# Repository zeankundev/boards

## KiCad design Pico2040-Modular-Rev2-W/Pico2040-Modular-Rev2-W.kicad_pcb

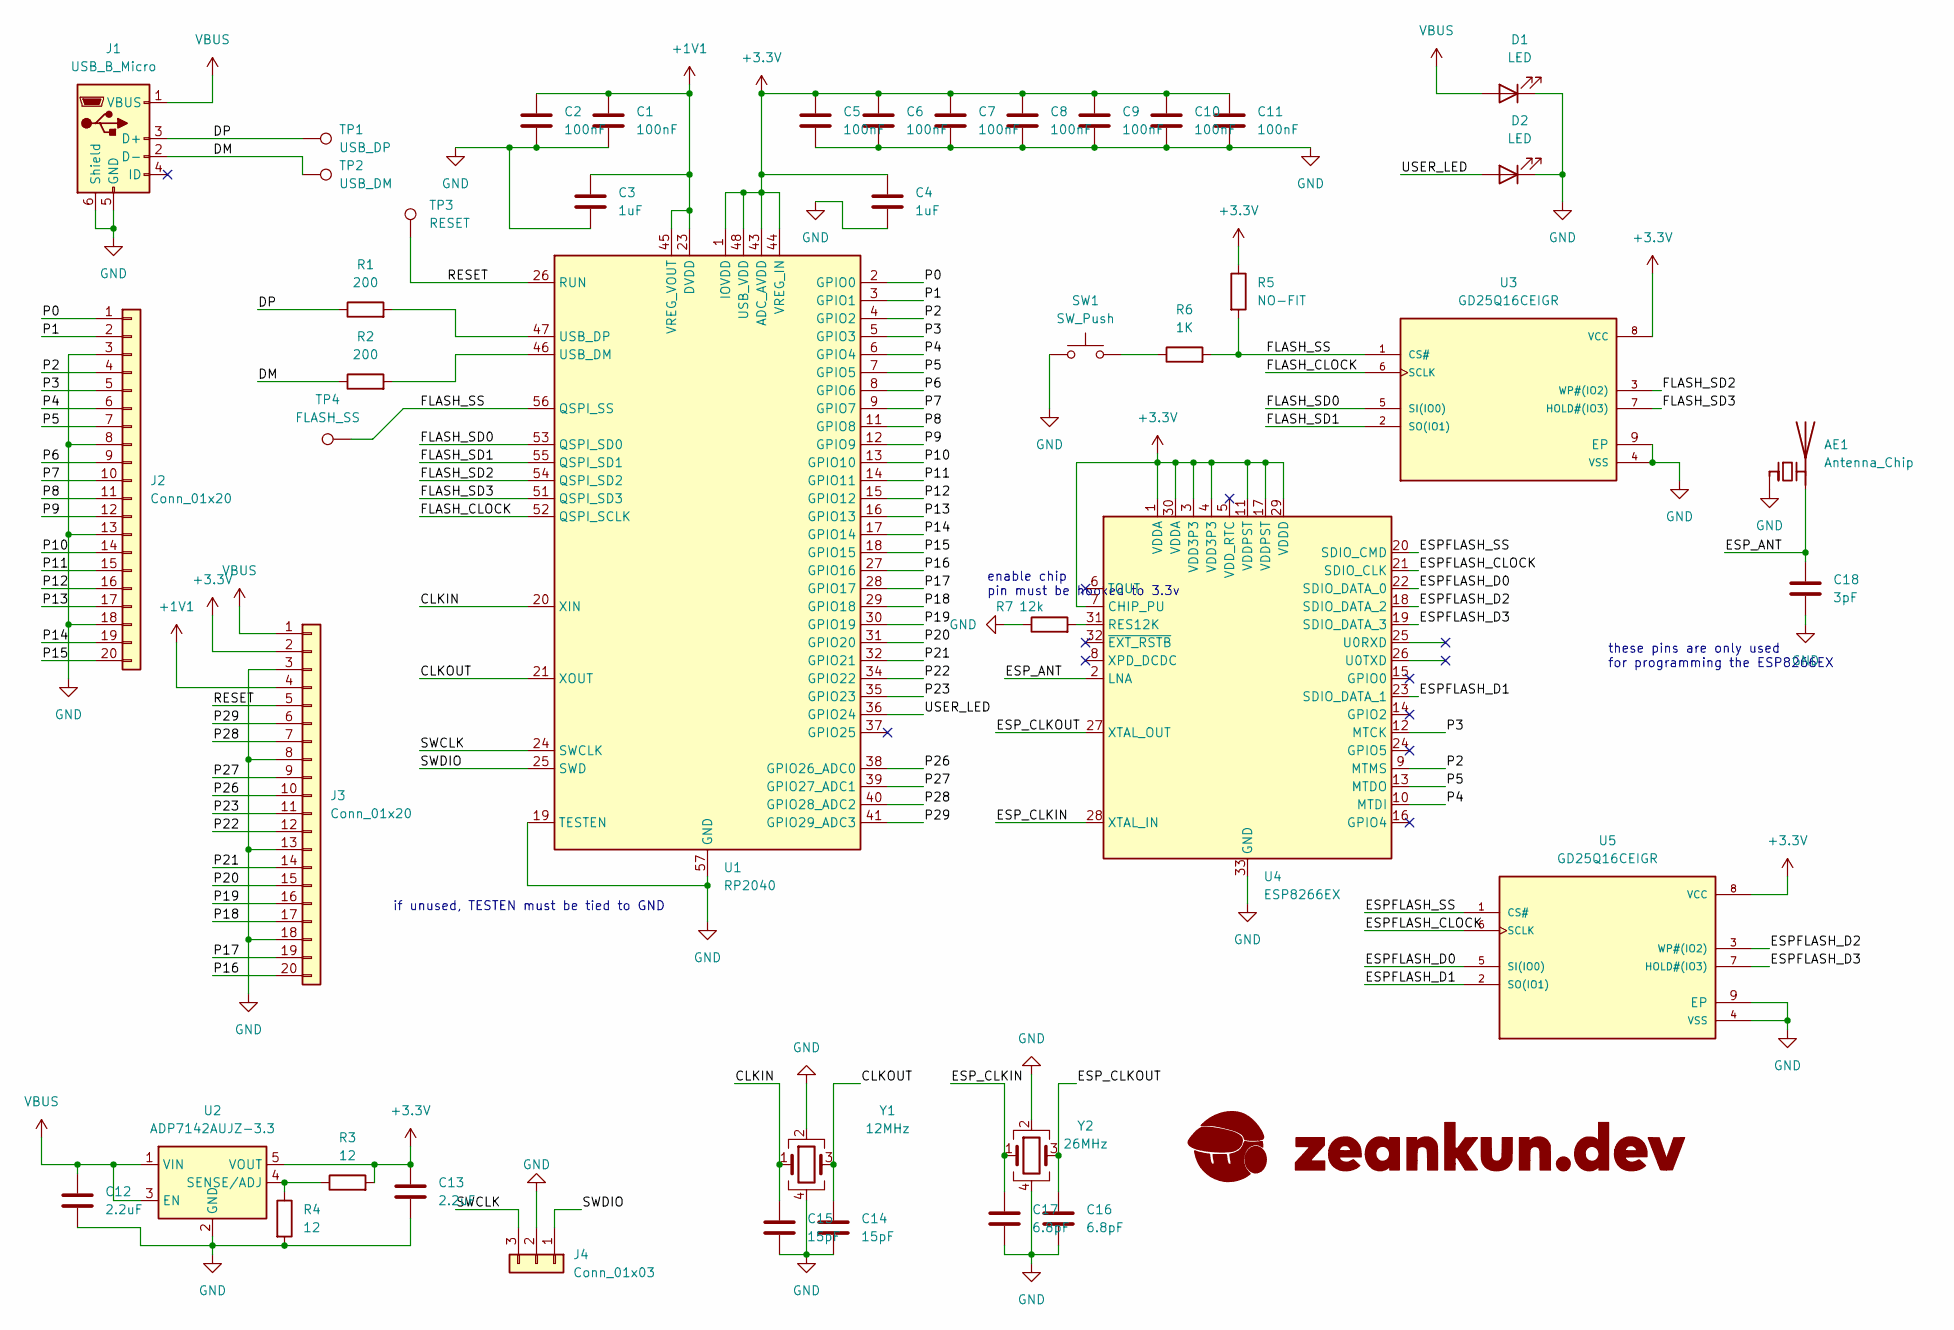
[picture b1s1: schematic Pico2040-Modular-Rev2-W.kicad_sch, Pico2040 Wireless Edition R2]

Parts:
AE1: Antenna_Chip; BroadWave_029mm
C1, C2, C5, C6, C7, C8, C9, C10, C11: 100nF; C_0201_0603Metric
C3, C4: 1uF; C_0201_0603Metric
C12, C13: 2.2uF; C_0201_0603Metric
C14, C15: 15pF; C_0201_0603Metric
C16, C17: 6.8pF; C_0201_0603Metric
C18: 3pF; C_0201_0603Metric
D1, D2: LED; LED_0201_0603Metric
J1: USB_B_Micro; USB_Micro-B_Amphenol_10103594-0001LF_Horizontal
J2, J3: Conn_01x20; PinHeader_1x20_2H_P2.54mm_Vertical
J4: Conn_01x03; PinHeader_1x03_P2.54mm_Vertical
R1, R2: 200; R_0201_0603Metric
R3, R4: 12; R_0201_0603Metric
R5: NO-FIT; R_0201_0603Metric
R6: 1K; R_0201_0603Metric
R7: 12k; R_0201_0603Metric
SW1: SW_Push; SW_Push_1P1T_NO_Vertical_Wuerth_434133025816
TP1: USB_DP; TestPoint_Pad_D1.0mm
TP2: USB_DM; TestPoint_Pad_D1.0mm
TP3: RESET; TestPoint_Pad_D1.0mm
TP4: FLASH_SS; TestPoint_Pad_D1.0mm
U1: RP2040; QFN-56-1EP_7x7mm_P0.4mm_EP3.2x3.2mm
U2: ADP7142AUJZ-3.3; TSOT-23-5
U3, U5: GD25Q16CEIGR; PSON50P200X300X50-9N; PARTREV 3.0
U4: ESP8266EX; QFN-32-1EP_5x5mm_P0.5mm_EP3.45x3.45mm
Y1: 12MHz; Crystal_SMD_2520-4Pin_2.5x2.0mm
Y2: 26MHz; Crystal_SMD_2016-4Pin_2.0x1.6mm

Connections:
+1V1: C1.1, C2.1, C3.1, J3.4, U1.23 (DVDD), U1.45 (VREG_VOUT), U1.50 (DVDD)
+3.3V: C4.1, C5.1, C6.1, C7.1, C8.1, C9.1, C10.1, C11.1, C13.1, J3.2, R3.2, R5.1, U1.1 (IOVDD), U1.10 (IOVDD), U1.22 (IOVDD), U1.33 (IOVDD), U1.42 (IOVDD), U1.43 (ADC_AVDD), U1.44 (VREG_IN), U1.48 (USB_VDD), U1.49 (IOVDD), U2.5 (VOUT), U3.8 (VCC), U4.1 (VDDA), U4.3 (VDD3P3), U4.4 (VDD3P3), U4.7 (CHIP_PU), U4.11 (VDDPST), U4.17 (VDDPST), U4.29 (VDDD), U4.30 (VDDA), U5.8 (VCC)
/CLKIN: C15.1, U1.20 (XIN), Y1.1
/CLKOUT: C14.1, U1.21 (XOUT), Y1.3
/DM: J1.2 (D-), R2.1, TP2.1
/DP: J1.3 (D+), R1.1, TP1.1
/ESPFLASH_CLOCK: U4.21 (SDIO_CLK), U5.6 (SCLK)
/ESPFLASH_D0: U4.22 (SDIO_DATA_0), U5.5 (SI(IO0))
/ESPFLASH_D1: U4.23 (SDIO_DATA_1), U5.2 (SO(IO1))
/ESPFLASH_D2: U4.18 (SDIO_DATA_2), U5.3 (WP#(IO2))
/ESPFLASH_D3: U4.19 (SDIO_DATA_3), U5.7 (HOLD#(IO3))
/ESPFLASH_SS: U4.20 (SDIO_CMD), U5.1 (CS#)
/ESP_ANT: AE1.2 (PCB_Trace), C18.1, U4.2 (LNA)
/ESP_CLKIN: C17.1, U4.28 (XTAL_IN), Y2.1
/ESP_CLKOUT: C16.1, U4.27 (XTAL_OUT), Y2.3
/FLASH_CLOCK: U1.52 (QSPI_SCLK), U3.6 (SCLK)
/FLASH_SD0: U1.53 (QSPI_SD0), U3.5 (SI(IO0))
/FLASH_SD1: U1.55 (QSPI_SD1), U3.2 (SO(IO1))
/FLASH_SD2: U1.54 (QSPI_SD2), U3.3 (WP#(IO2))
/FLASH_SD3: U1.51 (QSPI_SD3), U3.7 (HOLD#(IO3))
/FLASH_SS: R5.2, R6.2, TP4.1, U1.56 (QSPI_SS), U3.1 (CS#)
/P0: J2.1, U1.2 (GPIO0)
/P1: J2.2, U1.3 (GPIO1)
/P2: J2.4, U1.4 (GPIO2), U4.9 (MTMS)
/P3: J2.5, U1.5 (GPIO3), U4.12 (MTCK)
/P4: J2.6, U1.6 (GPIO4), U4.10 (MTDI)
/P5: J2.7, U1.7 (GPIO5), U4.13 (MTDO)
/P6: J2.9, U1.8 (GPIO6)
/P7: J2.10, U1.9 (GPIO7)
/P8: J2.11, U1.11 (GPIO8)
/P9: J2.12, U1.12 (GPIO9)
/P10: J2.14, U1.13 (GPIO10)
/P11: J2.15, U1.14 (GPIO11)
/P12: J2.16, U1.15 (GPIO12)
/P13: J2.17, U1.16 (GPIO13)
/P14: J2.19, U1.17 (GPIO14)
/P15: J2.20, U1.18 (GPIO15)
/P16: J3.20, U1.27 (GPIO16)
/P17: J3.19, U1.28 (GPIO17)
/P18: J3.17, U1.29 (GPIO18)
/P19: J3.16, U1.30 (GPIO19)
/P20: J3.15, U1.31 (GPIO20)
/P21: J3.14, U1.32 (GPIO21)
/P22: J3.12, U1.34 (GPIO22)
/P23: J3.11, U1.35 (GPIO23)
/P26: J3.10, U1.38 (GPIO26_ADC0)
/P27: J3.9, U1.39 (GPIO27_ADC1)
/P28: J3.7, U1.40 (GPIO28_ADC2)
/P29: J3.6, U1.41 (GPIO29_ADC3)
/RESET: J3.5, TP3.1, U1.26 (RUN)
/SWCLK: J4.3, U1.24 (SWCLK)
/SWDIO: J4.1, U1.25 (SWD)
/USER_LED: D2.2 (A), U1.36 (GPIO24)
GND: AE1.1 (FEED), C1.2, C2.2, C3.2, C4.2, C5.2, C6.2, C7.2, C8.2, C9.2, C10.2, C11.2, C12.2, C13.2, C14.2, C15.2, C16.2, C17.2, C18.2, D1.1 (K), D2.1 (K), J1.5 (GND), J1.6 (Shield), J2.3, J2.8, J2.13, J2.18, J3.3, J3.8, J3.13, J3.18, J4.2, R4.2, R7.1, SW1.1, U1.19 (TESTEN), U1.57 (GND), U2.2 (GND), U3.4 (VSS), U3.9 (EP), U4.33 (GND), U5.4 (VSS), U5.9 (EP), Y1.2, Y1.4, Y2.2, Y2.4
unnamed: R6.1, SW1.2
unnamed: R2.2, U1.46 (USB_DM)
unnamed: R1.2, U1.47 (USB_DP)
unnamed: R3.1, R4.1, U2.4 (SENSE/ADJ)
unnamed: R7.2, U4.31 (RES12K)
VBUS: C12.1, D1.2 (A), J1.1 (VBUS), J3.1, U2.1 (VIN), U2.3 (EN)

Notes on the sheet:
these pins are only used for programming the ESP8266EX
enable chip pin must be hooked to 3.3v
if unused, TESTEN must be tied to GND

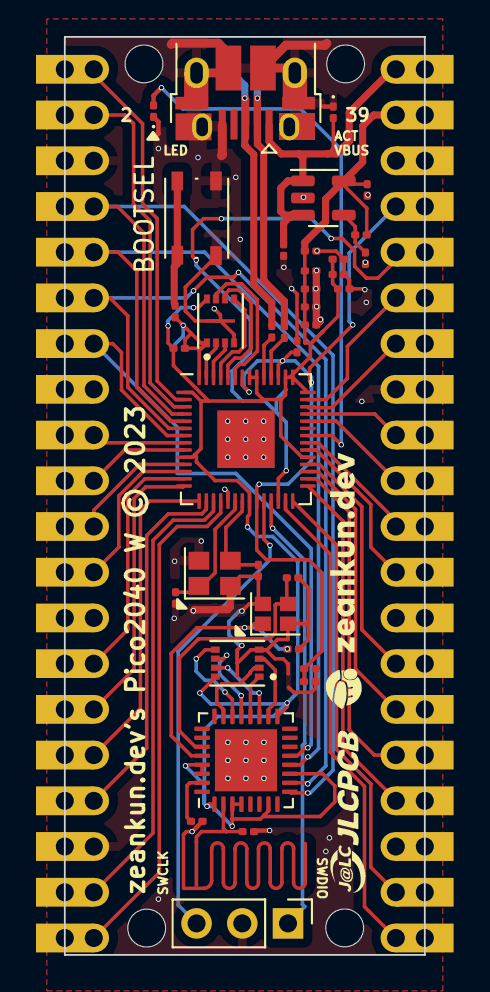
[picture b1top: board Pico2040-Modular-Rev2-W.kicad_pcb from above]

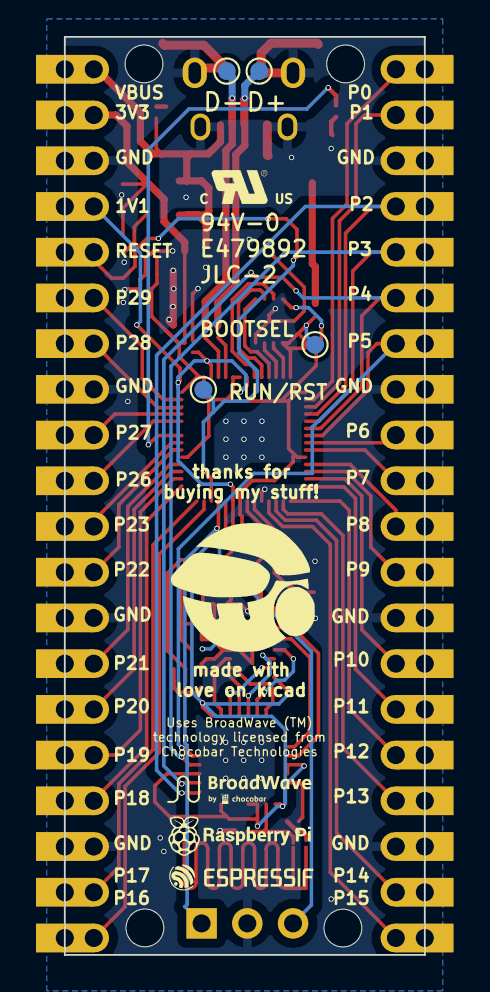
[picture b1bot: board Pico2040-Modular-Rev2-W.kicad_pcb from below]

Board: 2 copper layers, 20.0 x 51.0 mm, 44 parts (5 on the bottom side), 60 nets.

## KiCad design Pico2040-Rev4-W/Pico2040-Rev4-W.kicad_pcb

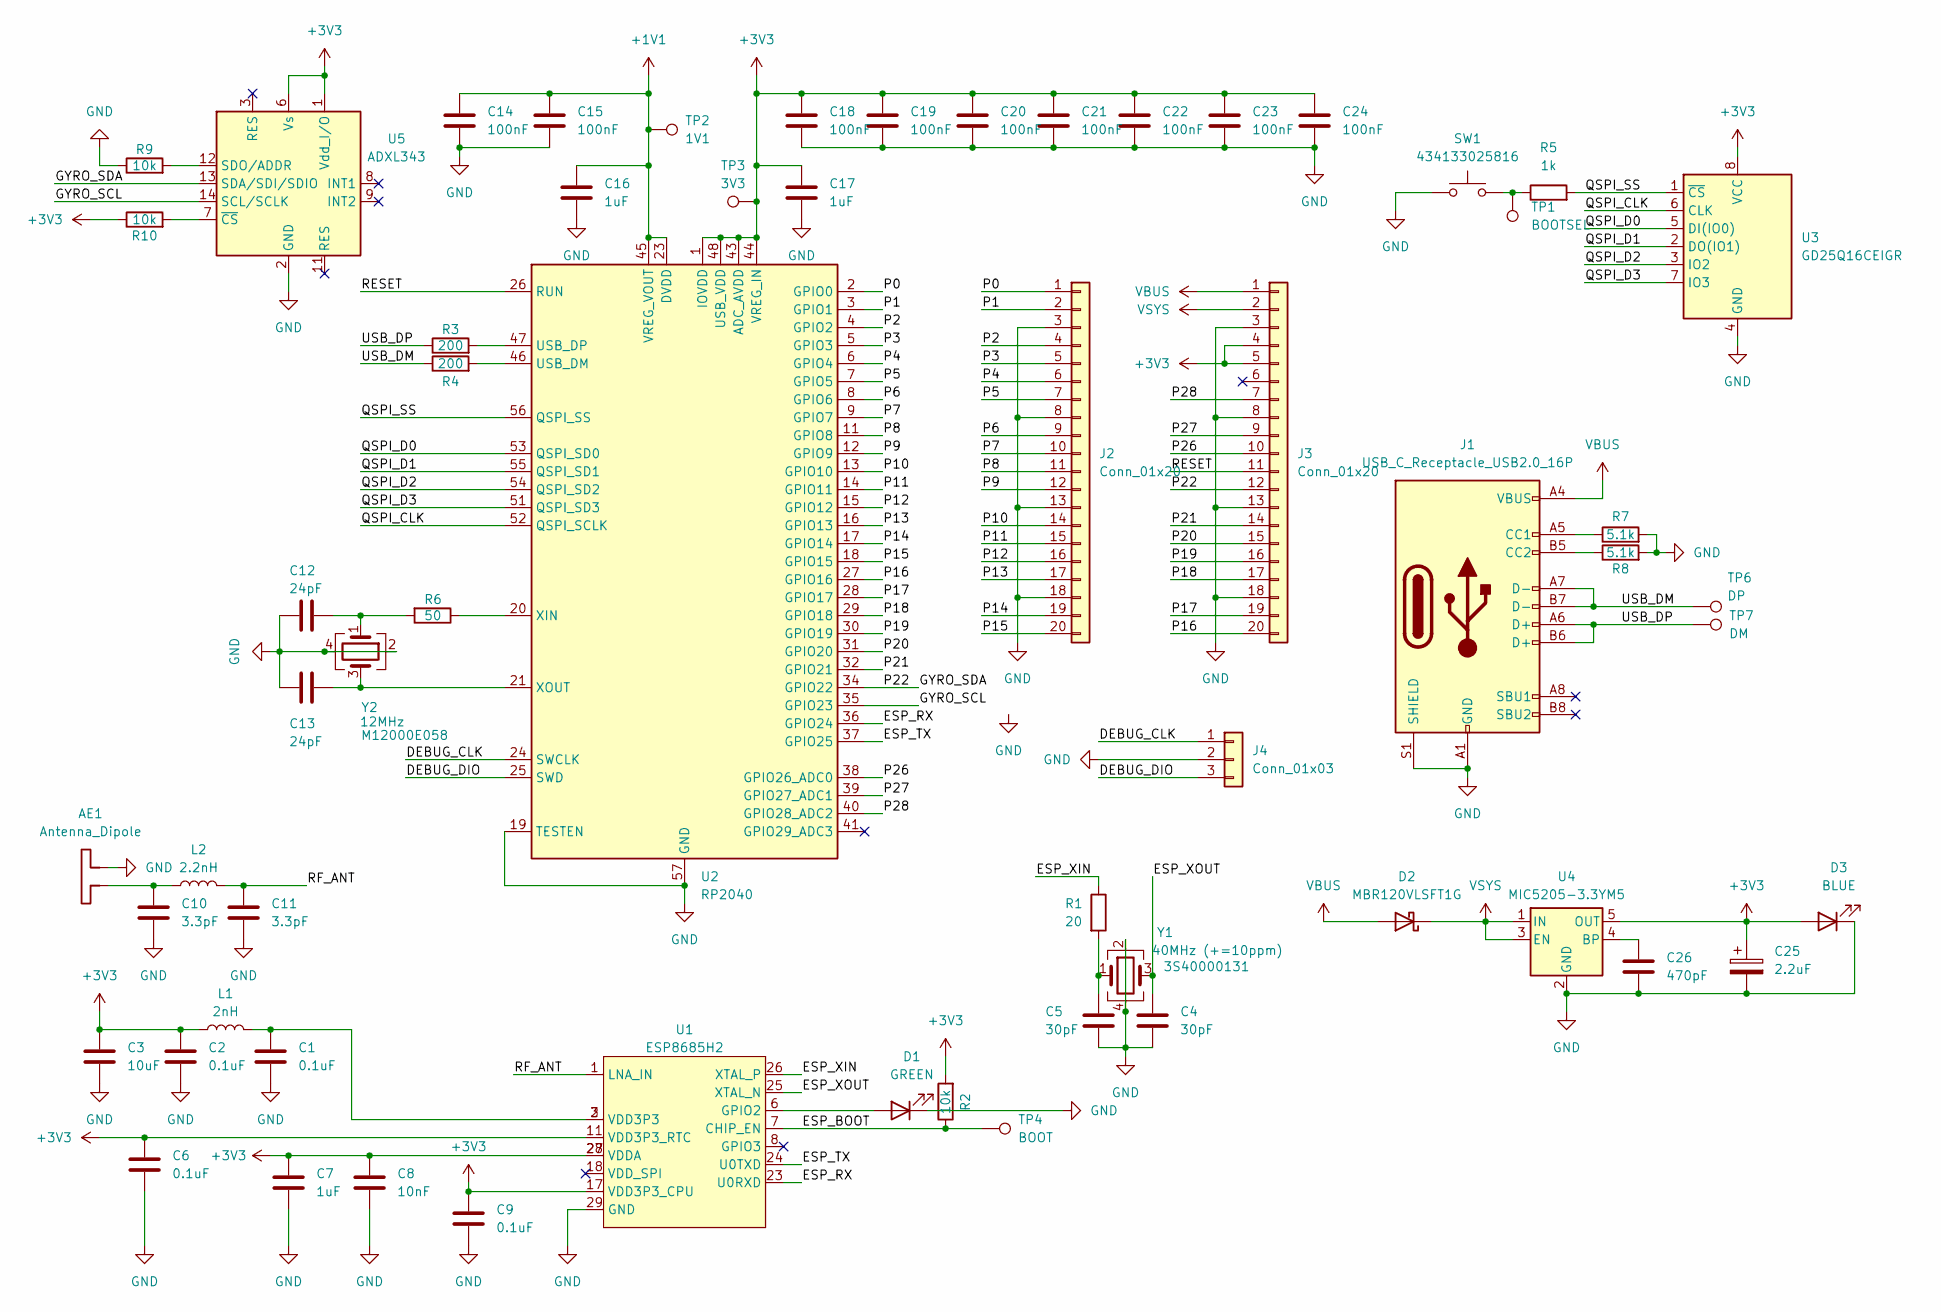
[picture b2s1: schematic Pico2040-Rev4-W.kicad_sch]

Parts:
AE1: Antenna_Dipole; Texas_SWRA117D_2.4GHz_Left
C1, C2, C6, C9: 0.1uF; C_0402_1005Metric
C3: 10uF; C_0402_1005Metric
C4, C5: 30pF; C_0402_1005Metric
C7, C16, C17: 1uF; C_0402_1005Metric
C8: 10nF; C_0402_1005Metric
C10, C11: 3.3pF; C_0402_1005Metric
C12, C13: 24pF; C_0402_1005Metric
C14, C15, C18, C19, C20, C21, C22, C23, C24: 100nF; C_0402_1005Metric
C25: 2.2uF; CP_EIA-1608-08_AVX-J
C26: 470pF; C_0402_1005Metric
D1: GREEN; LED_0402_1005Metric
D2: MBR120VLSFT1G; D_SOD-123F
D3: BLUE; LED_0402_1005Metric
J1: USB_C_Receptacle_USB2.0_16P; USB_C_Receptacle_GCT_USB4105-xx-A_16P_TopMnt_Horizontal
J2, J3: Conn_01x20; Conn_01x20_2.54mm
J4: Conn_01x03; PinHeader_1x03_P2.54mm_Vertical
L1: 2nH; L_0402_1005Metric
L2: 2.2nH; L_0402_1005Metric
R1: 20; R_0402_1005Metric
R2, R9, R10: 10k; R_0402_1005Metric
R3, R4: 200; R_0402_1005Metric
R5: 1k; R_0402_1005Metric
R6: 50; R_0402_1005Metric
R7, R8: 5.1k; R_0402_1005Metric
SW1: 434133025816; SW_Push_1P1T_NO_Vertical_Wuerth_434133025816
TP1: BOOTSEL; TestPoint_Pad_D1.0mm
TP2: 1V1; TestPoint_Pad_D1.0mm
TP3: 3V3; TestPoint_Pad_D1.0mm
TP4: BOOT; TestPoint_Pad_D1.0mm
TP6: DP; TestPoint_Pad_D1.0mm
TP7: DM; TestPoint_Pad_D1.0mm
U1: ESP8685H2; QFN-28-1EP_4x4mm_P0.4mm_EP2.4x2.4mm
U2: RP2040; QFN-56-1EP_7x7mm_P0.4mm_EP3.2x3.2mm
U3: GD25Q16CEIGR; 8-USON-2X3
U4: MIC5205-3.3YM5; SOT-23-5
U5: ADXL343; LGA-14_3x5mm_P0.8mm_LayoutBorder1x6y
Y1: 40MHz (+=10ppm); Crystal_SMD_3225-4Pin_3.2x2.5mm; Part Name 3S40000131
Y2: 12MHz; Crystal_SMD_3225-4Pin_3.2x2.5mm; Part Name M12000E058

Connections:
+1V1: C14.1, C15.1, C16.1, TP2.1, U2.23 (DVDD), U2.45 (VREG_VOUT), U2.50 (DVDD)
+3V3: C2.1, C3.1, C6.1, C7.1, C8.1, C9.1, C17.1, C18.1, C19.1, C20.1, C21.1, C22.1, C23.1, C24.1, C25.1, D3.2 (A), J3.4, J3.5, L1.1, R2.2, R10.1, TP3.1, U1.11 (VDD3P3_RTC), U1.17 (VDD3P3_CPU), U1.27 (VDDA), U1.28 (VDDA), U2.1 (IOVDD), U2.10 (IOVDD), U2.22 (IOVDD), U2.33 (IOVDD), U2.42 (IOVDD), U2.43 (ADC_AVDD), U2.44 (VREG_IN), U2.48 (USB_VDD), U2.49 (IOVDD), U3.8 (VCC), U4.5 (OUT), U5.1 (Vdd_I/O), U5.6 (Vs)
/DEBUG_CLK: J4.1, U2.24 (SWCLK)
/DEBUG_DIO: J4.3, U2.25 (SWD)
/ESP_BOOT: R2.1, TP4.1, U1.7 (CHIP_EN)
/ESP_RX: U1.23 (U0RXD), U2.36 (GPIO24)
/ESP_TX: U1.24 (U0TXD), U2.37 (GPIO25)
/ESP_XIN: R1.1, U1.26 (XTAL_P)
/ESP_XOUT: C4.1, U1.25 (XTAL_N), Y1.3
/GYRO_SCL: U2.35 (GPIO23), U5.14 (SCL/SCLK)
/GYRO_SDA: J3.12, U2.34 (GPIO22), U5.13 (SDA/SDI/SDIO)
/P0: J2.1, U2.2 (GPIO0)
/P1: J2.2, U2.3 (GPIO1)
/P2: J2.4, U2.4 (GPIO2)
/P3: J2.5, U2.5 (GPIO3)
/P4: J2.6, U2.6 (GPIO4)
/P5: J2.7, U2.7 (GPIO5)
/P6: J2.9, U2.8 (GPIO6)
/P7: J2.10, U2.9 (GPIO7)
/P8: J2.11, U2.11 (GPIO8)
/P9: J2.12, U2.12 (GPIO9)
/P10: J2.14, U2.13 (GPIO10)
/P11: J2.15, U2.14 (GPIO11)
/P12: J2.16, U2.15 (GPIO12)
/P13: J2.17, U2.16 (GPIO13)
/P14: J2.19, U2.17 (GPIO14)
/P15: J2.20, U2.18 (GPIO15)
/P16: J3.20, U2.27 (GPIO16)
/P17: J3.19, U2.28 (GPIO17)
/P18: J3.17, U2.29 (GPIO18)
/P19: J3.16, U2.30 (GPIO19)
/P20: J3.15, U2.31 (GPIO20)
/P21: J3.14, U2.32 (GPIO21)
/P26: J3.10, U2.38 (GPIO26_ADC0)
/P27: J3.9, U2.39 (GPIO27_ADC1)
/P28: J3.7, U2.40 (GPIO28_ADC2)
/QSPI_CLK: U2.52 (QSPI_SCLK), U3.6 (CLK)
/QSPI_D0: U2.53 (QSPI_SD0), U3.5 (DI(IO0))
/QSPI_D1: U2.55 (QSPI_SD1), U3.2 (DO(IO1))
/QSPI_D2: U2.54 (QSPI_SD2), U3.3 (IO2)
/QSPI_D3: U2.51 (QSPI_SD3), U3.7 (IO3)
/QSPI_SS: R5.2, U2.56 (QSPI_SS), U3.1 (~CS)
/RESET: J3.11, U2.26 (RUN)
/RF_ANT: C11.1, L2.2, U1.1 (LNA_IN)
/USB_DM: J1.A7 (D-), J1.B7 (D-), R4.1, TP6.1
/USB_DP: J1.A6 (D+), J1.B6 (D+), R3.1, TP7.1
GND: AE1.2, C1.2, C2.2, C3.2, C4.2, C5.2, C6.2, C7.2, C8.2, C9.2, C10.2, C11.2, C12.2, C13.2, C14.2, C15.2, C16.2, C17.2, C18.2, C19.2, C20.2, C21.2, C22.2, C23.2, C24.2, C25.2, C26.2, D1.1 (K), D3.1 (K), J1.A1 (GND), J1.A12 (GND), J1.B1 (GND), J1.B12 (GND), J1.S1 (SHIELD), J2.3, J2.8, J2.13, J2.18, J3.3, J3.8, J3.13, J3.18, J4.2, R7.2, R8.2, R9.1, SW1.1, U1.29 (GND), U2.19 (TESTEN), U2.57 (GND), U3.4 (GND), U4.2 (GND), U5.2 (GND), U5.4 (GND), U5.5 (GND), Y1.2, Y1.4, Y2.2, Y2.4
unnamed: AE1.1, C10.1, L2.1
unnamed: C1.1, L1.2, U1.2 (VDD3P3), U1.3 (VDD3P3)
unnamed: C5.1, R1.2, Y1.1
unnamed: C12.1, R6.2, Y2.1
unnamed: D1.2 (A), U1.6 (GPIO2)
unnamed: J1.A5 (CC1), R7.1
unnamed: J1.B5 (CC2), R8.1
unnamed: R5.1, SW1.2, TP1.1
unnamed: R4.2, U2.46 (USB_DM)
unnamed: R3.2, U2.47 (USB_DP)
unnamed: R6.1, U2.20 (XIN)
unnamed: C13.1, U2.21 (XOUT), Y2.3
unnamed: C26.1, U4.4 (BP)
unnamed: R9.2, U5.12 (SDO/ADDR)
unnamed: R10.2, U5.7 (~CS)
VBUS: D2.2 (A), J1.A4 (VBUS), J1.A9 (VBUS), J1.B4 (VBUS), J1.B9 (VBUS), J3.1
VSYS: D2.1 (K), J3.2, U4.1 (IN), U4.3 (EN)

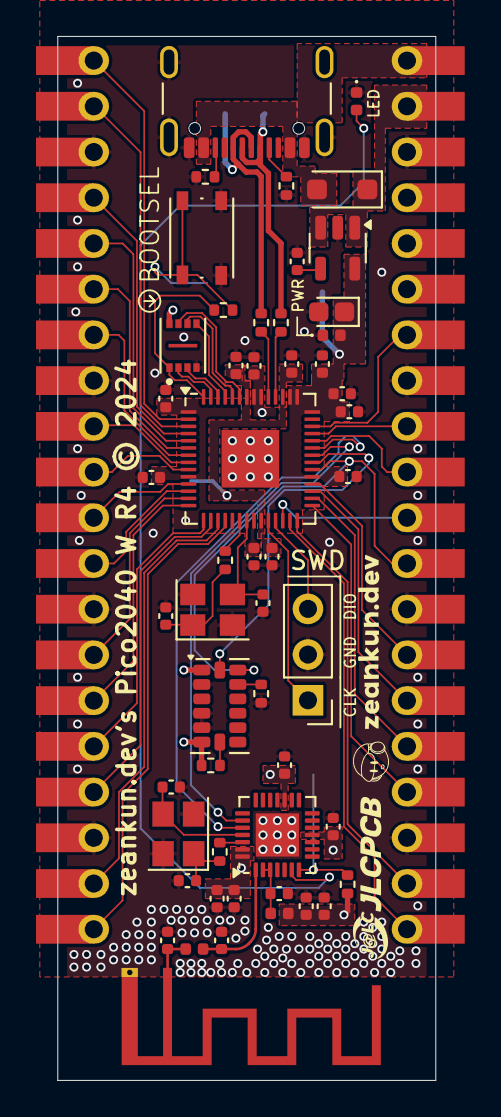
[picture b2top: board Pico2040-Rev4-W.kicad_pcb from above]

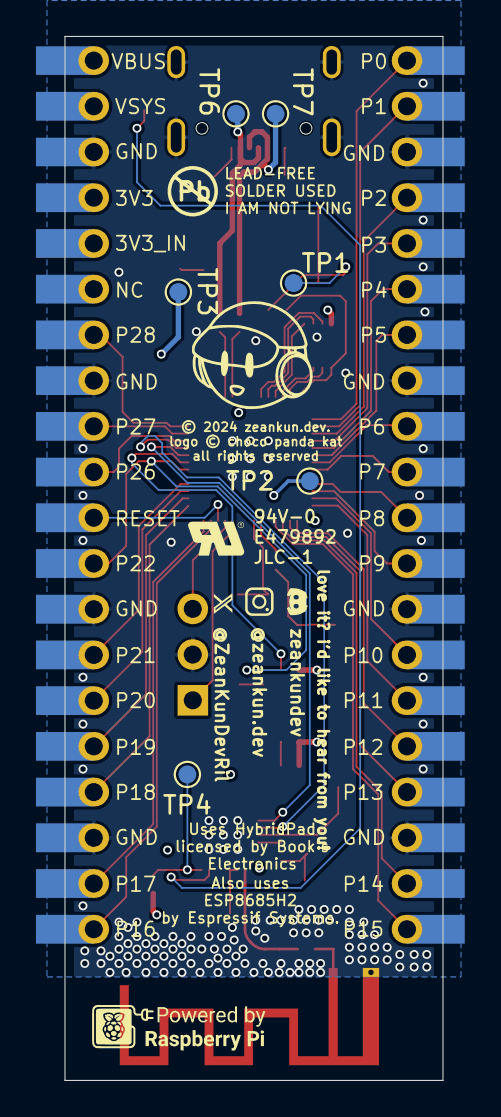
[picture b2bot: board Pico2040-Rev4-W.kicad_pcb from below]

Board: 4 copper layers, 21.0 x 58.0 mm, 60 parts (7 on the bottom side), 64 nets.

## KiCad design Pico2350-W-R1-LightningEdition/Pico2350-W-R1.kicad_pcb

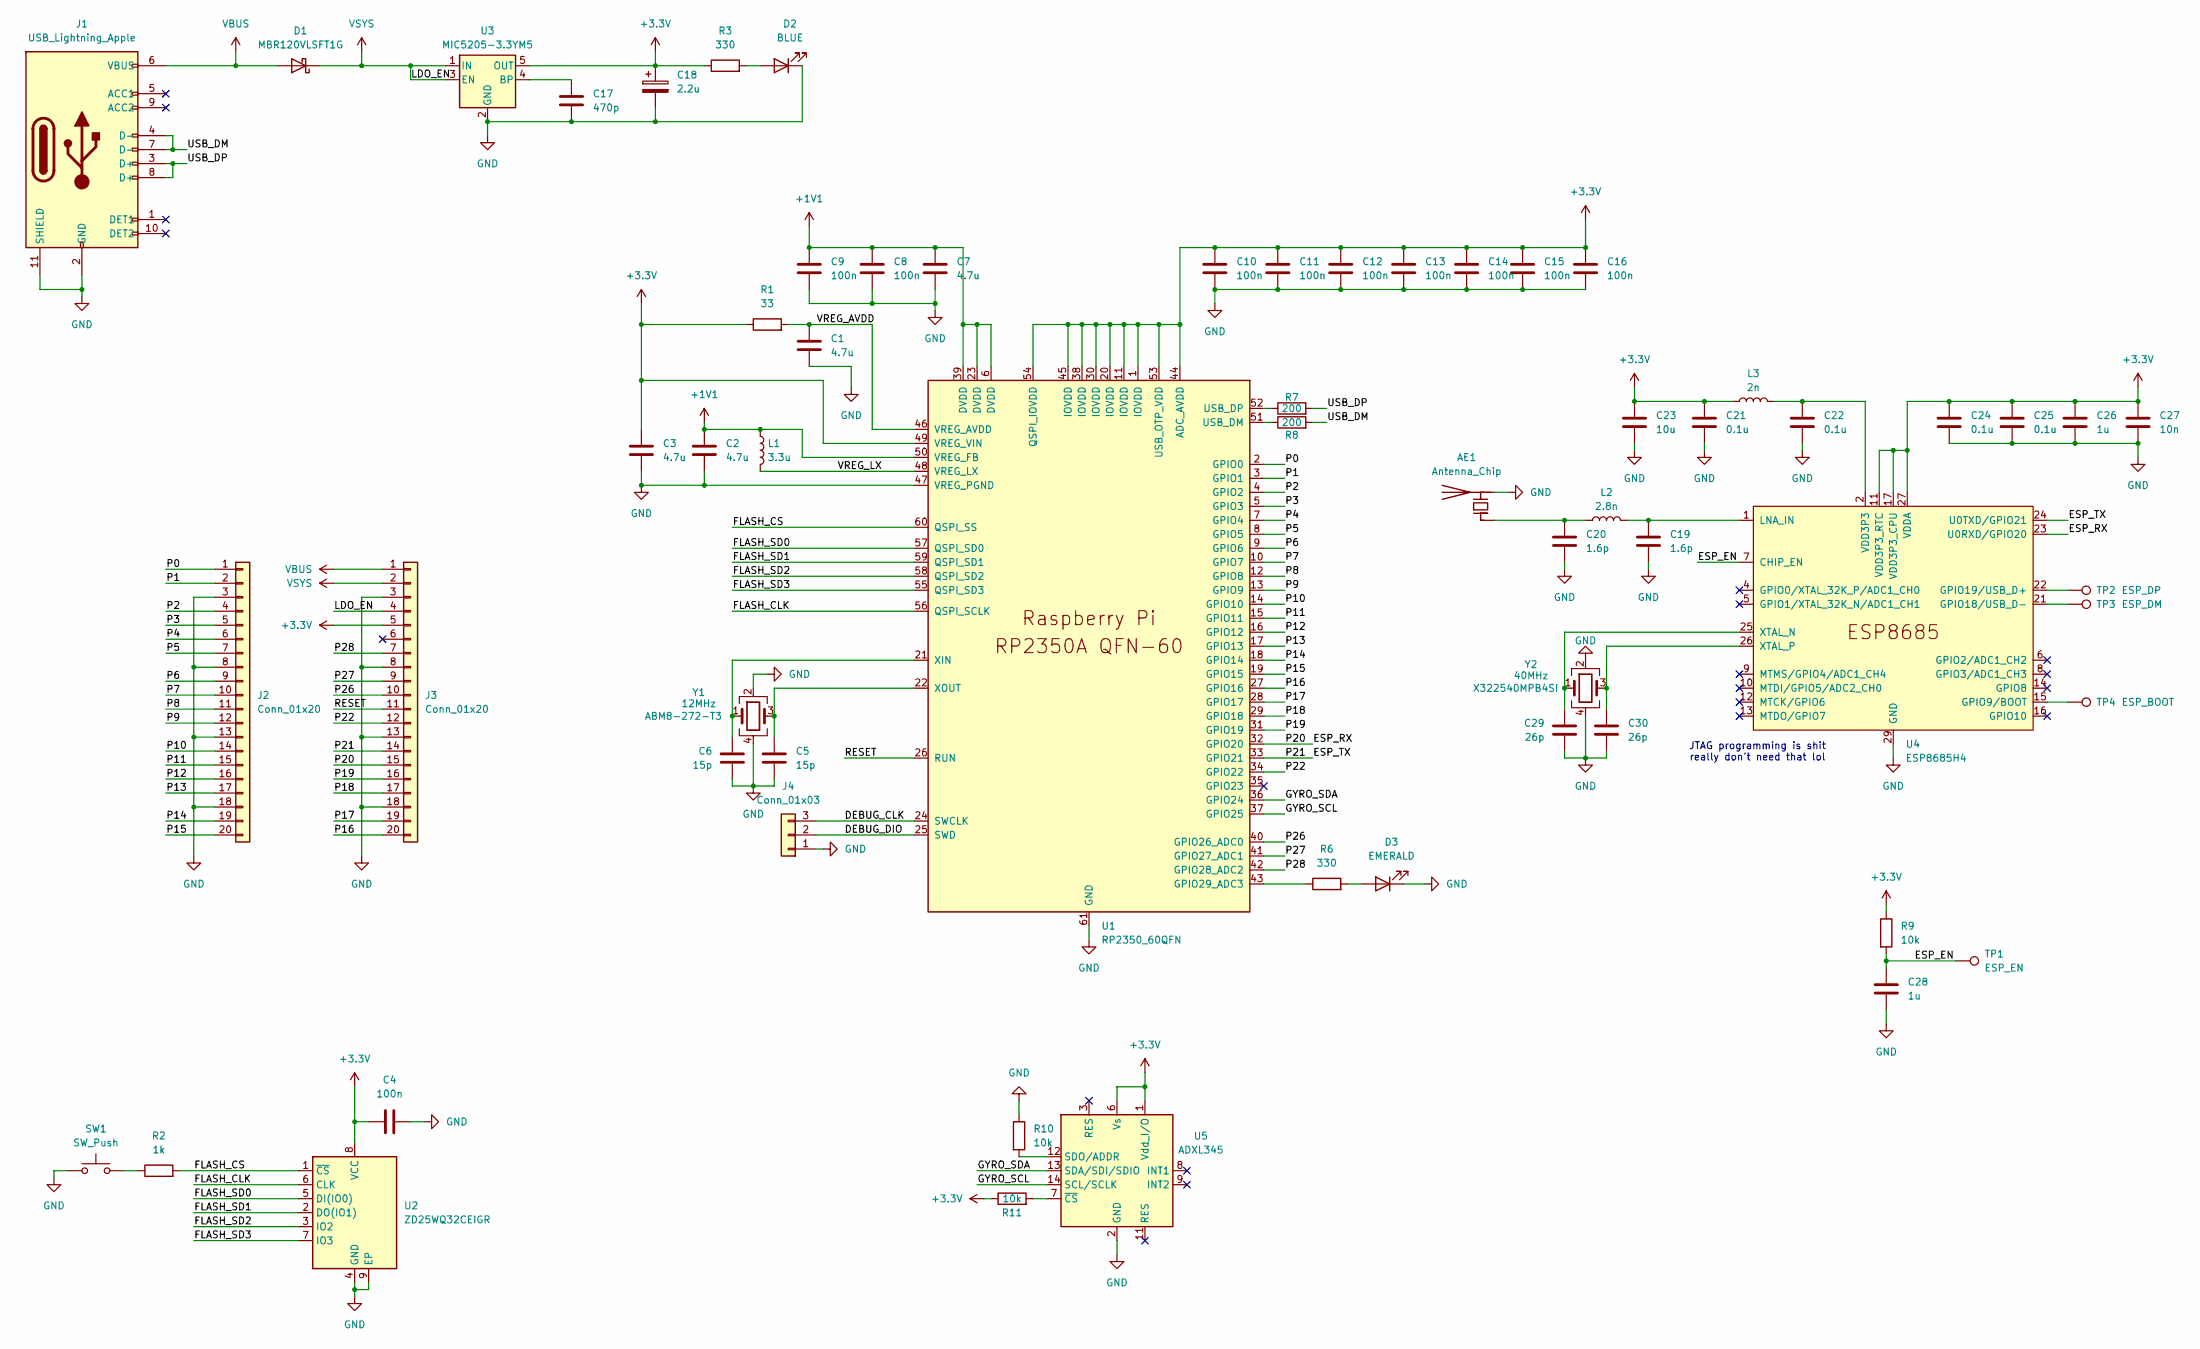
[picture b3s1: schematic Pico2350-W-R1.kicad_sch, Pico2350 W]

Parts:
AE1: Antenna_Chip; Texas_SWRA117D_2.4GHz_Left
C1, C2, C3, C7: 4.7u; C_0402_1005Metric
C4, C8, C9, C10, C11, C12, C13, C14, C15, C16: 100n; C_0402_1005Metric
C5, C6: 15p; C_0402_1005Metric
C17: 470p; C_0402_1005Metric
C18: 2.2u; CP_EIA-2012-12_Kemet-R
C19, C20: 1.6p; C_0402_1005Metric
C21, C22, C24, C25: 0.1u; C_0402_1005Metric
C23: 10u; C_0402_1005Metric
C26, C28: 1u; C_0402_1005Metric
C27: 10n; C_0402_1005Metric
C29, C30: 26p; C_0402_1005Metric
D1: MBR120VLSFT1G; D_SOD-123F
D2: BLUE; LED_0402_1005Metric
D3: EMERALD; LED_0402_1005Metric
J1: USB_Lightning_Apple; Apple_LightningConnector_ShouHan
J2, J3: Conn_01x20; 1x20_2.54mm
J4: Conn_01x03; PinHeader_1x03_P2.54mm_Vertical
L1: 3.3u; L_pol_2016
L2: 2.8n; L_0402_1005Metric
L3: 2n; L_0402_1005Metric
R1: 33; R_0402_1005Metric
R2: 1k; R_0402_1005Metric
R3, R6: 330; R_0402_1005Metric
R7, R8: 200; R_0402_1005Metric
R9, R10, R11: 10k; R_0402_1005Metric
SW1: SW_Push; SW_Push_1P1T_NO_Vertical_Wuerth_434133025816
TP1: ESP_EN; TestPoint_Pad_D1.0mm
TP2: ESP_DP; TestPoint_Pad_D1.0mm
TP3: ESP_DM; TestPoint_Pad_D1.0mm
TP4: ESP_BOOT; TestPoint_Pad_D1.0mm
U1: RP2350_60QFN; RP2350-QFN-60-1EP_7x7_P0.4mm_EP3.4x3.4mm_ThermalVias
U2: ZD25WQ32CEIGR; 8-USON-2X3
U3: MIC5205-3.3YM5; SOT-23-5
U4: ESP8685H4; QFN-28-1EP_4x4mm_P0.4mm_EP2.6x2.6mm
U5: ADXL345; LGA-14_3x5mm_P0.8mm_LayoutBorder1x6y
Y1: 12MHz; Crystal_SMD_3225-4Pin_3.2x2.5mm
Y2: 40MHz; Crystal_SMD_3225-4Pin_3.2x2.5mm

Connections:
+1V1: C2.1, C7.1, C8.1, C9.1, L1.1, U1.6 (DVDD), U1.23 (DVDD), U1.39 (DVDD), U1.50 (VREG_FB)
+3.3V: C3.1, C4.1, C10.1, C11.1, C12.1, C13.1, C14.1, C15.1, C16.1, C18.1, C21.1, C23.1, C24.1, C25.1, C26.1, C27.1, J3.5, L3.1, R1.1, R3.1, R9.1, R11.1, U1.1 (IOVDD), U1.11 (IOVDD), U1.20 (IOVDD), U1.30 (IOVDD), U1.38 (IOVDD), U1.44 (ADC_AVDD), U1.45 (IOVDD), U1.49 (VREG_VIN), U1.53 (USB_OTP_VDD), U1.54 (QSPI_IOVDD), U2.8 (VCC), U3.5 (OUT), U4.11 (VDD3P3_RTC), U4.17 (VDD3P3_CPU), U4.27 (VDDA), U4.28 (VDDA), U5.1 (Vdd_I/O), U5.6 (Vs)
/DEBUG_CLK: J4.3, U1.24 (SWCLK)
/DEBUG_DIO: J4.2, U1.25 (SWD)
/ESP_EN: C28.1, R9.2, TP1.1, U4.7 (CHIP_EN)
/ESP_RX: J3.15, U1.32 (GPIO20), U4.23 (U0RXD/GPIO20)
/ESP_TX: J3.14, U1.33 (GPIO21), U4.24 (U0TXD/GPIO21)
/FLASH_CLK: U1.56 (QSPI_SCLK), U2.6 (CLK)
/FLASH_CS: R2.2, U1.60 (QSPI_SS), U2.1 (~CS)
/FLASH_SD0: U1.57 (QSPI_SD0), U2.5 (DI(IO0))
/FLASH_SD1: U1.59 (QSPI_SD1), U2.2 (DO(IO1))
/FLASH_SD2: U1.58 (QSPI_SD2), U2.3 (IO2)
/FLASH_SD3: U1.55 (QSPI_SD3), U2.7 (IO3)
/GYRO_SCL: U1.37 (GPIO25), U5.14 (SCL/SCLK)
/GYRO_SDA: U1.36 (GPIO24), U5.13 (SDA/SDI/SDIO)
/P0: J2.1, U1.2 (GPIO0)
/P1: J2.2, U1.3 (GPIO1)
/P2: J2.4, U1.4 (GPIO2)
/P3: J2.5, U1.5 (GPIO3)
/P4: J2.6, U1.7 (GPIO4)
/P5: J2.7, U1.8 (GPIO5)
/P6: J2.9, U1.9 (GPIO6)
/P7: J2.10, U1.10 (GPIO7)
/P8: J2.11, U1.12 (GPIO8)
/P9: J2.12, U1.13 (GPIO9)
/P10: J2.14, U1.14 (GPIO10)
/P11: J2.15, U1.15 (GPIO11)
/P12: J2.16, U1.16 (GPIO12)
/P13: J2.17, U1.17 (GPIO13)
/P14: J2.19, U1.18 (GPIO14)
/P15: J2.20, U1.19 (GPIO15)
/P16: J3.20, U1.27 (GPIO16)
/P17: J3.19, U1.28 (GPIO17)
/P18: J3.17, U1.29 (GPIO18)
/P19: J3.16, U1.31 (GPIO19)
/P22: J3.12, U1.34 (GPIO22)
/P26: J3.10, U1.40 (GPIO26_ADC0)
/P27: J3.9, U1.41 (GPIO27_ADC1)
/P28: J3.7, U1.42 (GPIO28_ADC2)
/RESET: J3.11, U1.26 (RUN)
/USB_DM: J1.4 (D-), J1.7 (D-), R8.2
/USB_DP: J1.3 (D+), J1.8 (D+), R7.2
/VREG_AVDD: C1.1, R1.2, U1.46 (VREG_AVDD)
/VREG_LX: L1.2, U1.48 (VREG_LX)
GND: AE1.2 (PCB_Trace), C1.2, C2.2, C3.2, C4.2, C5.2, C6.2, C7.2, C8.2, C9.2, C10.2, C11.2, C12.2, C13.2, C14.2, C15.2, C16.2, C17.2, C18.2, C19.2, C20.2, C21.2, C22.2, C23.2, C24.2, C25.2, C26.2, C27.2, C28.2, C29.2, C30.2, D2.1 (K), D3.1 (K), J1.2 (GND), J1.11 (SHIELD), J1.12 (SHIELD), J1.13 (SHIELD), J1.14 (SHIELD), J2.3, J2.8, J2.13, J2.18, J3.3, J3.8, J3.13, J3.18, J4.1, R10.1, SW1.1, U1.47 (VREG_PGND), U1.61 (GND), U2.4 (GND), U2.9 (EP), U3.2 (GND), U4.29 (GND), U5.2 (GND), U5.4 (GND), U5.5 (GND), Y1.2, Y1.4, Y2.2, Y2.4
unnamed: AE1.1 (FEED), C20.1, L2.1
unnamed: C22.1, L3.2, U4.2 (VDD3P3), U4.3 (VDD3P3)
unnamed: D2.2 (A), R3.2
unnamed: D3.2 (A), R6.2
unnamed: R2.1, SW1.2
unnamed: R6.1, U1.43 (GPIO29_ADC3)
unnamed: R8.1, U1.51 (USB_DM)
unnamed: R7.1, U1.52 (USB_DP)
unnamed: C6.1, U1.21 (XIN), Y1.1
unnamed: C5.1, U1.22 (XOUT), Y1.3
unnamed: C17.1, U3.4 (BP)
unnamed: TP4.1, U4.15 (GPIO9/BOOT)
unnamed: TP3.1, U4.21 (GPIO18/USB_D-)
unnamed: TP2.1, U4.22 (GPIO19/USB_D+)
unnamed: C19.1, L2.2, U4.1 (LNA_IN)
unnamed: C29.1, U4.25 (XTAL_N), Y2.1
unnamed: C30.1, U4.26 (XTAL_P), Y2.3
unnamed: R10.2, U5.12 (SDO/ADDR)
unnamed: R11.2, U5.7 (~CS)
VBUS: D1.2 (A), J1.6 (VBUS), J3.1
VSYS: D1.1 (K), J3.2, J3.4, U3.1 (IN), U3.3 (EN)

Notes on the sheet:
JTAG programming is shit really don't need that lol

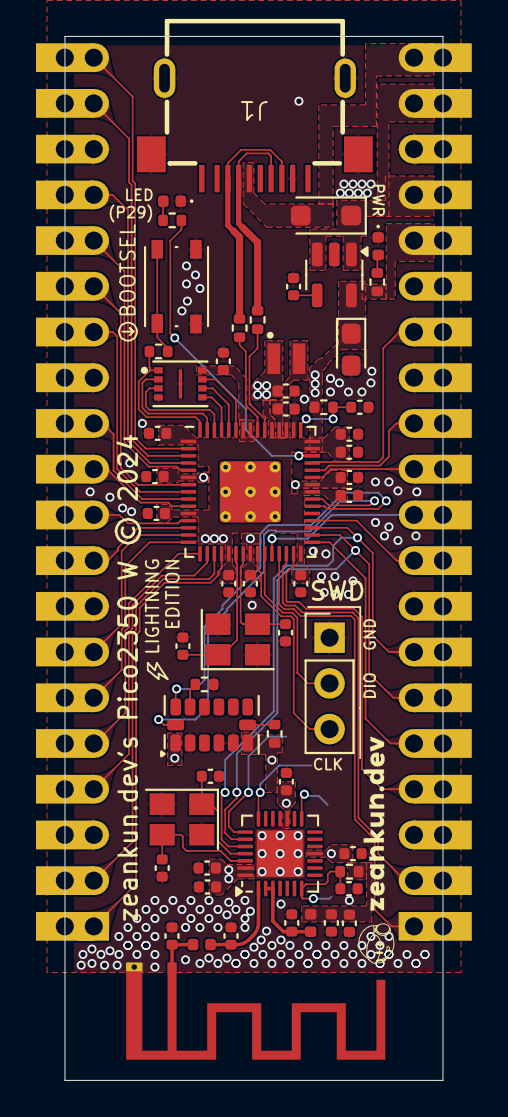
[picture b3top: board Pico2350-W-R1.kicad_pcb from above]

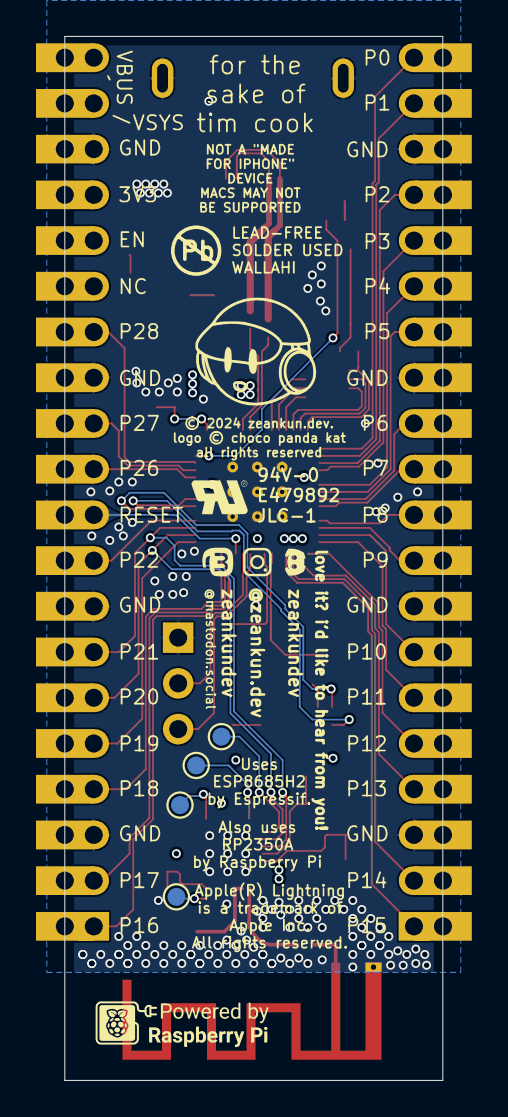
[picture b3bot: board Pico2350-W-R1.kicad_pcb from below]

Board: 4 copper layers, 21.0 x 58.0 mm, 62 parts (5 on the bottom side), 66 nets.

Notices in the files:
Pico2040-Modular-Rev2-W/Pico2040-Modular-Rev2-W.kicad_pcb:
zeankun.dev's Pico2040 W © 2023
Pico2040-Rev4-W/Pico2040-Rev4-W.kicad_pcb:
licensed by Book's
©️ 2024 zeankun.dev.
logo ©️ choco panda kat
all rights reserved
zeankun.dev's Pico2040 W R4 © 2024
Pico2350-W-R1-LightningEdition/Pico2350-W-R1.kicad_pcb:
zeankun.dev's Pico2350 W © 2024
Pico2350-W-R1-LightningEdition/Pico2350-W-R1.kicad_sch:
Copyright (c) 2024 zeankun.dev
